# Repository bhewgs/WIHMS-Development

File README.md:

# WIHMS-Development

This repository serves as the open source location for development of the Wearable Integrated Health Monitoring System (WIHMS) garment. This effort was funded by the Vermont Space Grant Consortium under NASA Cooperative Agreement NNX15AP86H. Sensors currently incorporated in the garment are linked below:  
Gravity 3 Lead Heart Rate Monitor: https://amzn.to/2YntU75  
MAXIM30102 Particle Sensor: https://amzn.to/2Srb2R8  
Vishay Thermistor: https://bit.ly/3b1BSWt  
SSD1306 128x32 OLED Display: https://amzn.to/35nHatQ  
DS3231 Real Time Clock: https://amzn.to/3d59WSF  
Moisture Sensor Custom Board: https://github.com/bhewgs/WIHMS-Development/tree/master/MoistureSensor  
Data Consolidation Board Design Files: https://github.com/bhewgs/WIHMS-Development/tree/master/Version%202%20SOIC8%20TCA9517  

Blake Hewgill, MS Student
Jeff Frolik, EBE Department Chair
Ryan McGinnis, Faculty Advisor
M-Sense Research Group: https://www.uvm.edu/~rsmcginn/  
Sensor Networks and Wireless Laboratory   
Direct correspondence to Blake Hewgill: bhewgill94@gmail.com

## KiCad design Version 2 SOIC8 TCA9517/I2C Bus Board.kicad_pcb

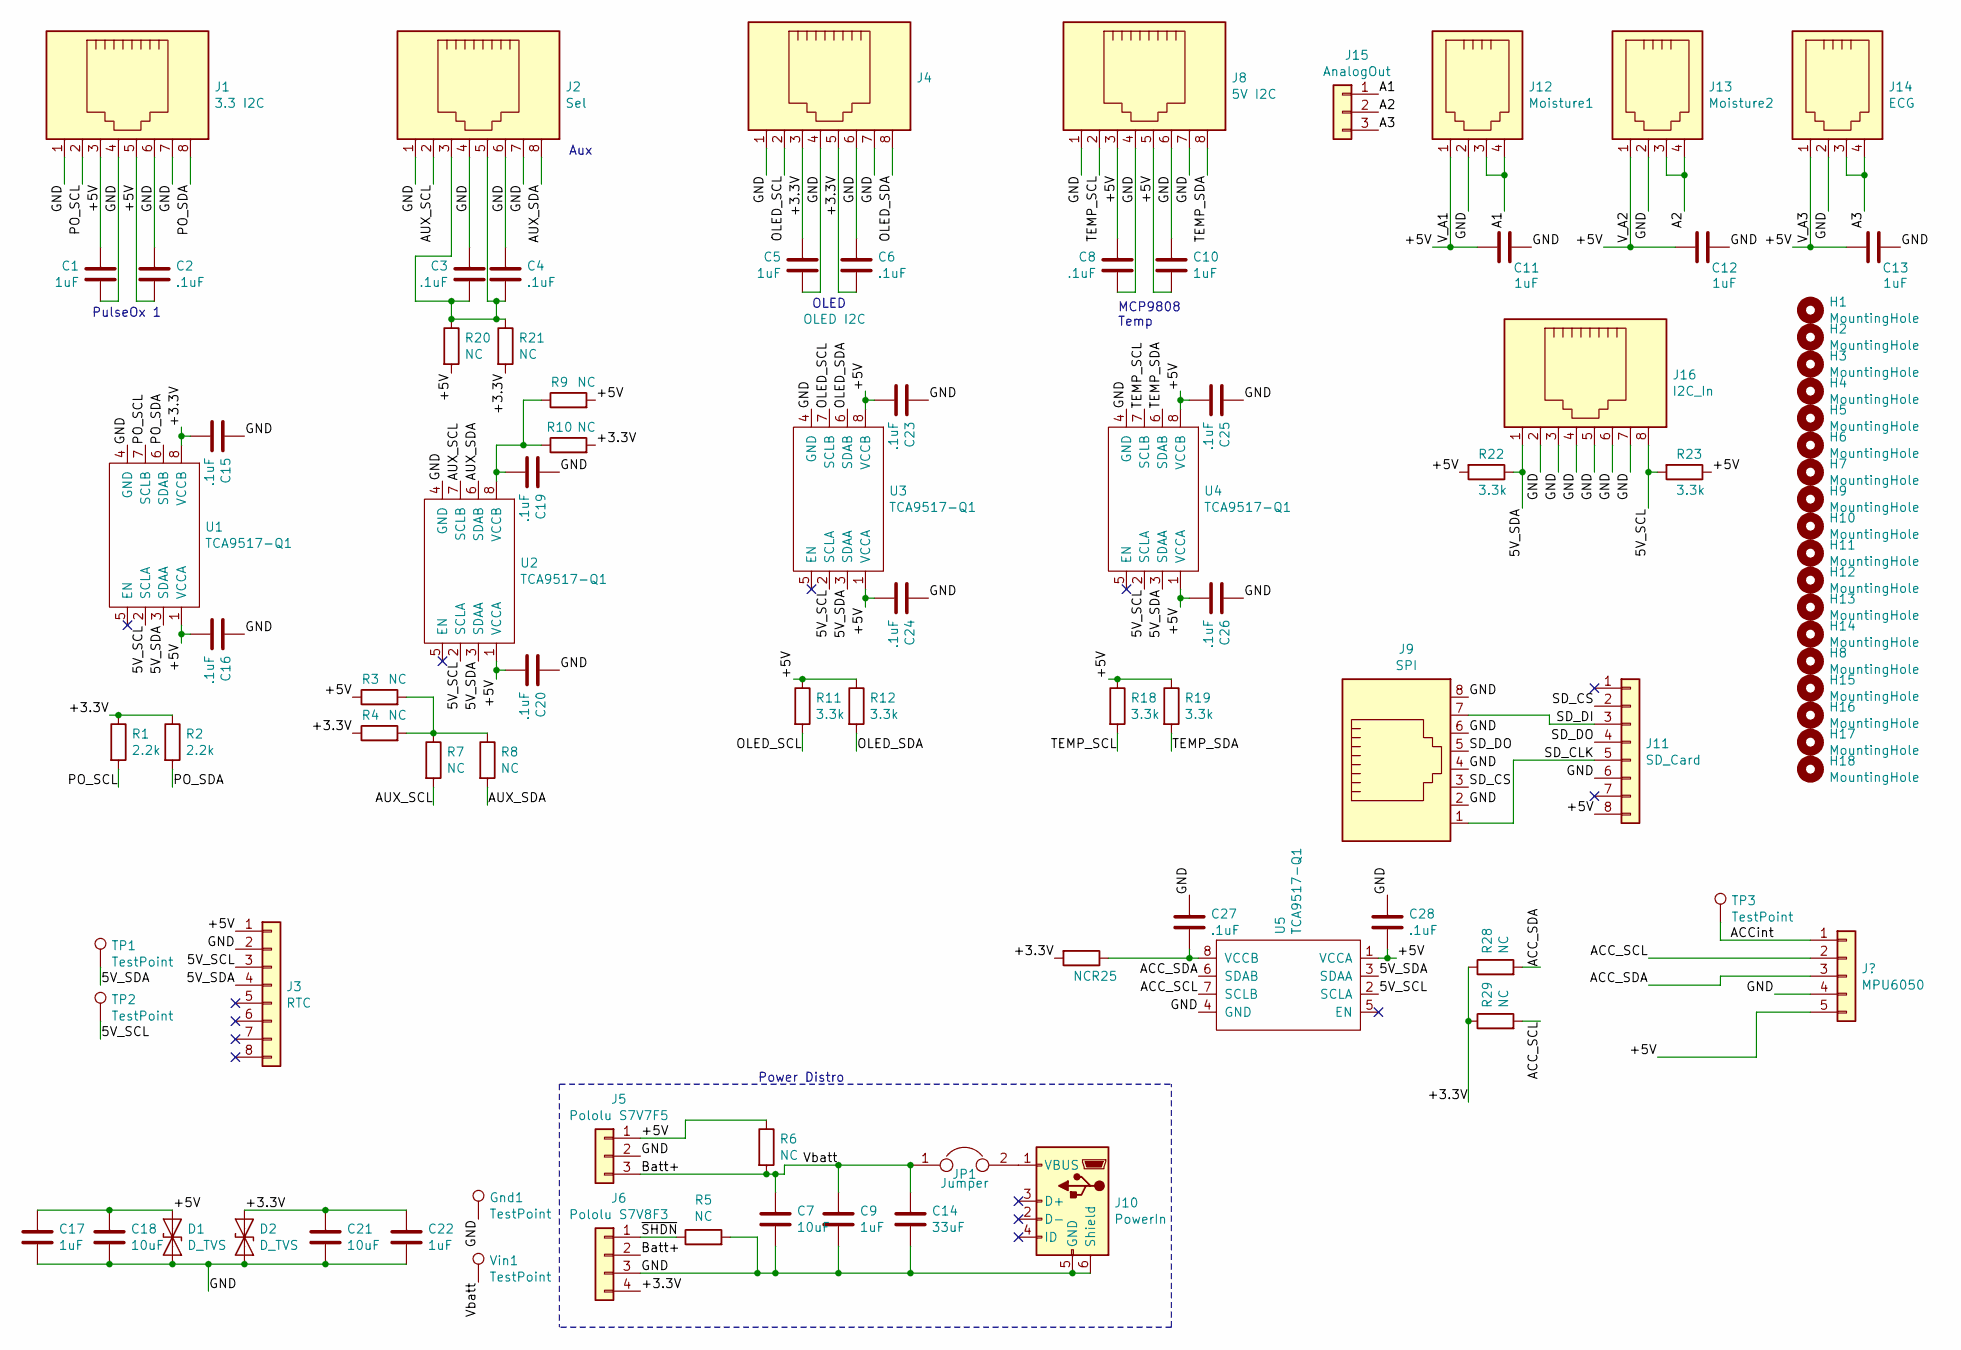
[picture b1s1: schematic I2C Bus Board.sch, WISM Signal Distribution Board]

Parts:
C1, C5, C9, C10, C11, C12, C13, C17, C22: 1uF; C_0603_1608Metric_Pad1.05x0.95mm_HandSolder
C2, C3, C4, C6, C8, C15, C16, C19, C20, C23, C24, C25, C26, C27, C28: .1uF; C_0603_1608Metric_Pad1.05x0.95mm_HandSolder
C7, C18, C21: 10uF; C_0603_1608Metric_Pad1.05x0.95mm_HandSolder
C14: 33uF; C_0805_2012Metric_Pad1.15x1.40mm_HandSolder
D1, D2: D_TVS; D_1206_3216Metric_Pad1.42x1.75mm_HandSolder
Gnd1: TestPoint; TestPoint_Loop_D1.80mm_Drill1.0mm_Beaded
H1, H2, H3, H4, H5, H6, H7, H8, H9, H10, H11, H12, H13, H14, H15, H16, H17, H18: MountingHole; MountingHole_2.2mm_M2
J1: 3.3 I2C; RJ45_Amphenol_54602-x08_Horizontal
J2: Sel; RJ45_Amphenol_54602-x08_Horizontal
J3: RTC; PinHeader_1x08_P2.54mm_Vertical
J4: OLED I2C; RJ45_Amphenol_54602-x08_Horizontal
J5: Pololu S7V7F5; PinHeader_1x03_P2.54mm_Vertical
J6: Pololu S7V8F3; PinHeader_1x04_P2.54mm_Vertical
J8: 5V I2C; RJ45_Amphenol_54602-x08_Horizontal
J9: SPI; RJ45_Amphenol_54602-x08_Horizontal
J10: PowerIn; USB_Micro-B_Wuerth_629105150521_CircularHoles
J11: SD_Card; PinHeader_1x08_P2.54mm_Vertical
J12: Moisture1; 4p4c
J13: Moisture2; 4p4c
J14: ECG; 4p4c
J15: AnalogOut; PinHeader_1x03_P2.54mm_Vertical
J16: I2C_In; RJ45_Amphenol_54602-x08_Horizontal
JP1: Jumper; PinHeader_1x02_P2.54mm_Vertical
R1, R2: 2.2k; R_0603_1608Metric_Pad1.05x0.95mm_HandSolder
R3, R4, R5, R7, R8, R9, R10, R20, R21, R25, R28, R29: NC; R_0603_1608Metric_Pad1.05x0.95mm_HandSolder
R6: NC; SolderJumper-2_P1.3mm_Open_RoundedPad1.0x1.5mm
R11, R12, R18, R19, R22, R23: 3.3k; R_0603_1608Metric_Pad1.05x0.95mm_HandSolder
TP1, TP2, TP3: TestPoint; TestPoint_Loop_D1.80mm_Drill1.0mm_Beaded
U1, U2, U3, U4, U5: TCA9517-Q1; SOIC-8_3.9x4.9mm_P1.27mm
Vin1: TestPoint; TestPoint_Loop_D1.80mm_Drill1.0mm_Beaded

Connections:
/5V_SCL: J3.3, J16.8, R23.2, TP2.1, U1.2 (SCLA), U2.2 (SCLA), U3.2 (SCLA), U4.2 (SCLA), U5.2 (SCLA)
/5V_SDA: J3.4, J16.1, R22.1, TP1.1, U1.3 (SDAA), U2.3 (SDAA), U3.3 (SDAA), U4.3 (SDAA), U5.3 (SDAA)
/A1: J12.3, J12.4, J15.1
/A2: J13.3, J13.4, J15.2
/A3: J14.3, J14.4, J15.3
/ACC_SCL: R29.2, U5.7 (SCLB); also elsewhere on the board
/ACC_SDA: R28.2, U5.6 (SDAB); also elsewhere on the board
/ACCint: TP3.1; also elsewhere on the board
/AUX_SCL: J2.2, R7.2, U2.7 (SCLB)
/AUX_SDA: J2.8, R8.2, U2.6 (SDAB)
/Batt+: C7.1, C9.1, C14.1, J5.3, J6.2, JP1.1, R6.2, Vin1.1
/GND: C1.1, C2.1, C3.2, C4.1, C5.1, C6.1, C7.2, C8.1, C9.2, C10.1, C11.1, C12.1, C13.1, C14.2, C15.1, C16.1, C17.2, C18.2, C19.1, C20.1, C21.2, C22.2, C23.1, C24.1, C25.1, C26.1, C27.1, C28.1, D1.2 (A2), D2.2 (A2), Gnd1.1, J1.1, J1.4, J1.6, J1.7, J2.1, J2.4, J2.6, J2.7, J3.2, J4.1, J4.4, J4.6, J4.7, J5.2, J6.3, J8.1, J8.4, J8.6, J8.7, J9.2, J9.4, J9.6, J9.8, J10.5 (GND), J10.6 (Shield), J11.6, J12.2, J13.2, J14.2, J16.2, J16.3, J16.4, J16.5, J16.6, J16.7, R5.2, U1.4 (GND), U2.4 (GND), U3.4 (GND), U4.4 (GND), U5.4 (GND); also elsewhere on the board
/OLED_SCL: J4.2, R11.2, U3.7 (SCLB)
/OLED_SDA: J4.8, R12.2, U3.6 (SDAB)
/PO_SCL: J1.2, R1.2, U1.7 (SCLB)
/PO_SDA: J1.8, R2.2, U1.6 (SDAB)
/SD_CLK: J9.1, J11.5
/SD_CS: J9.3, J11.2
/SD_DI: J9.7, J11.3
/SD_DO: J9.5, J11.4
/TEMP_SCL: J8.2, R18.2, U4.7 (SCLB)
/TEMP_SDA: J8.8, R19.2, U4.6 (SDAB)
/~SHDN: J6.1, R5.1
unnamed: C3.1, C4.2, J2.3, J2.5, R20.1, R21.1
unnamed: C19.2, R9.1, R10.1, U2.8 (VCCB)
unnamed 25: C27.2, R25.1, U5.8 (VCCB); also elsewhere on the board
unnamed: J10.1 (VBUS), JP1.2
unnamed: R3.2, R4.2, R7.1, R8.1

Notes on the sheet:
MCP9808 Temp
PulseOx 1
Aux
Power Distro
OLED

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
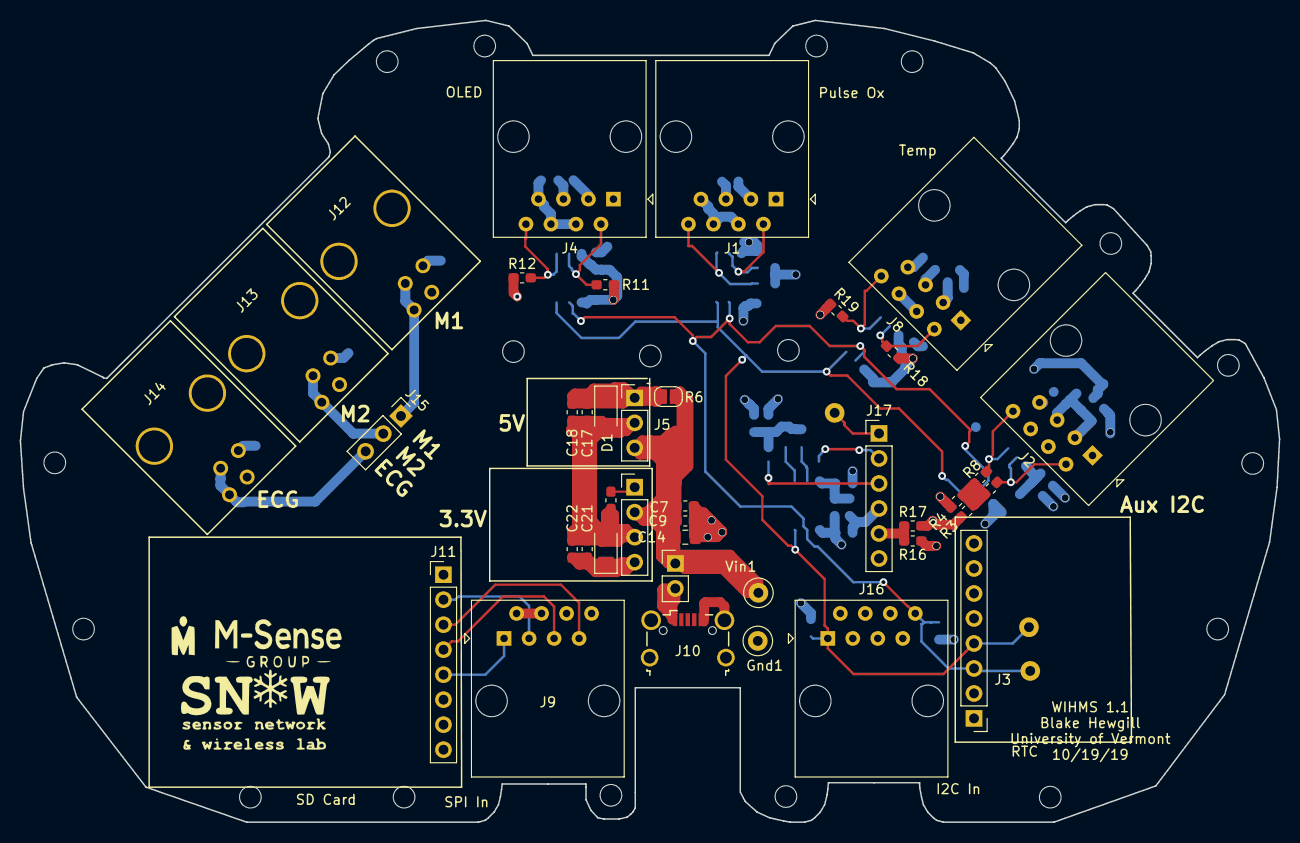
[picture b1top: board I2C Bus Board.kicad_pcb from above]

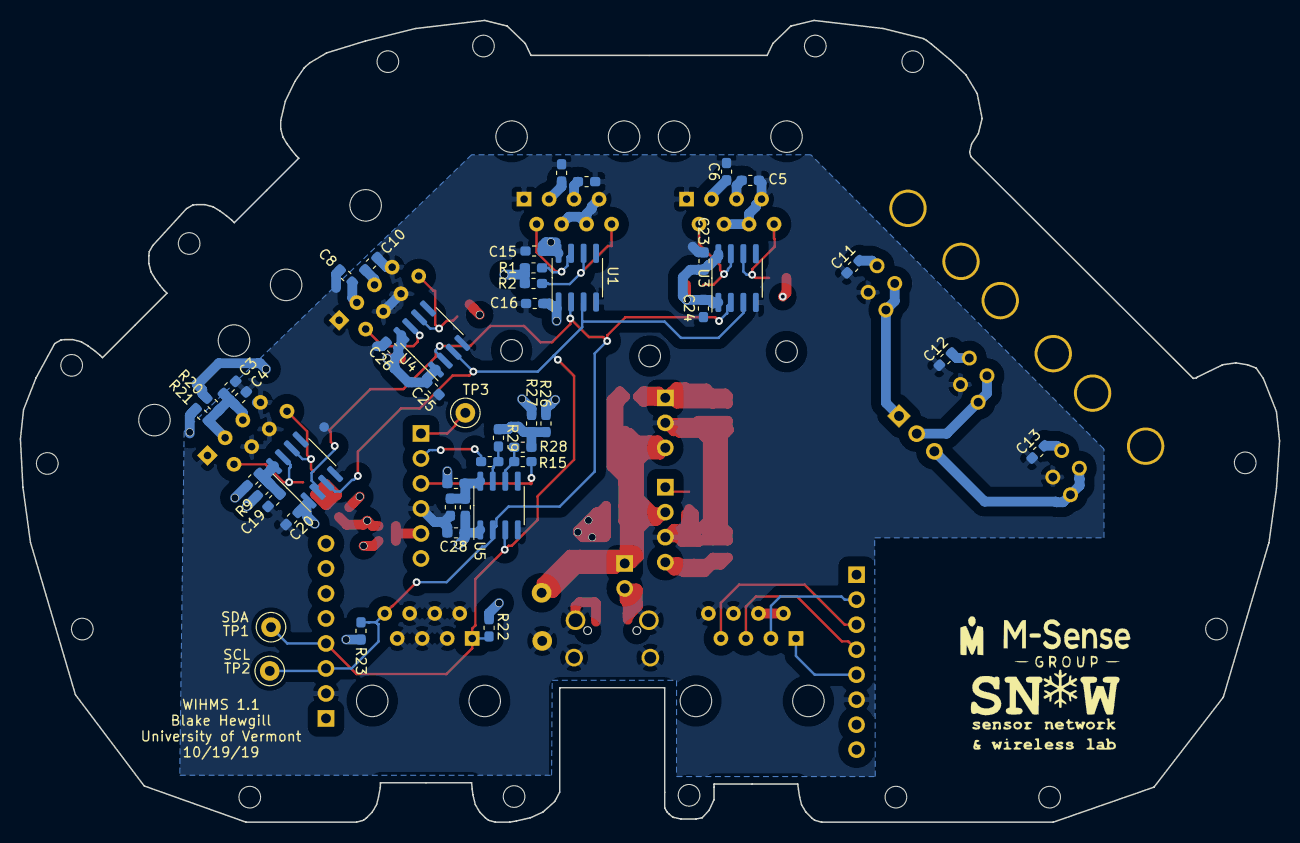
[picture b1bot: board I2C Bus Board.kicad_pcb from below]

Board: 4 copper layers, 128.0 x 81.5 mm, 103 parts (45 on the bottom side), 34 nets.

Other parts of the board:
J17: MPU6050; PinHeader_1x06_P2.54mm_Vertical
R14, R15, R16, R17, R24: 0; R_0603_1608Metric_Pad1.05x0.95mm_HandSolder
R26, R27: NC; R_0603_1608Metric_Pad1.05x0.95mm_HandSolder

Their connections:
/ACC_SCL: R14.2; also elsewhere on the board
/ACC_SDA: R15.2; also elsewhere on the board
/ACCint: J17.1; also elsewhere on the board
/GND: J17.4; also elsewhere on the board
unnamed 25: R24.1; also elsewhere on the board
unnamed: J17.2, R14.1
unnamed: J17.3, R15.1
unnamed: J17.5, R16.1, R17.1

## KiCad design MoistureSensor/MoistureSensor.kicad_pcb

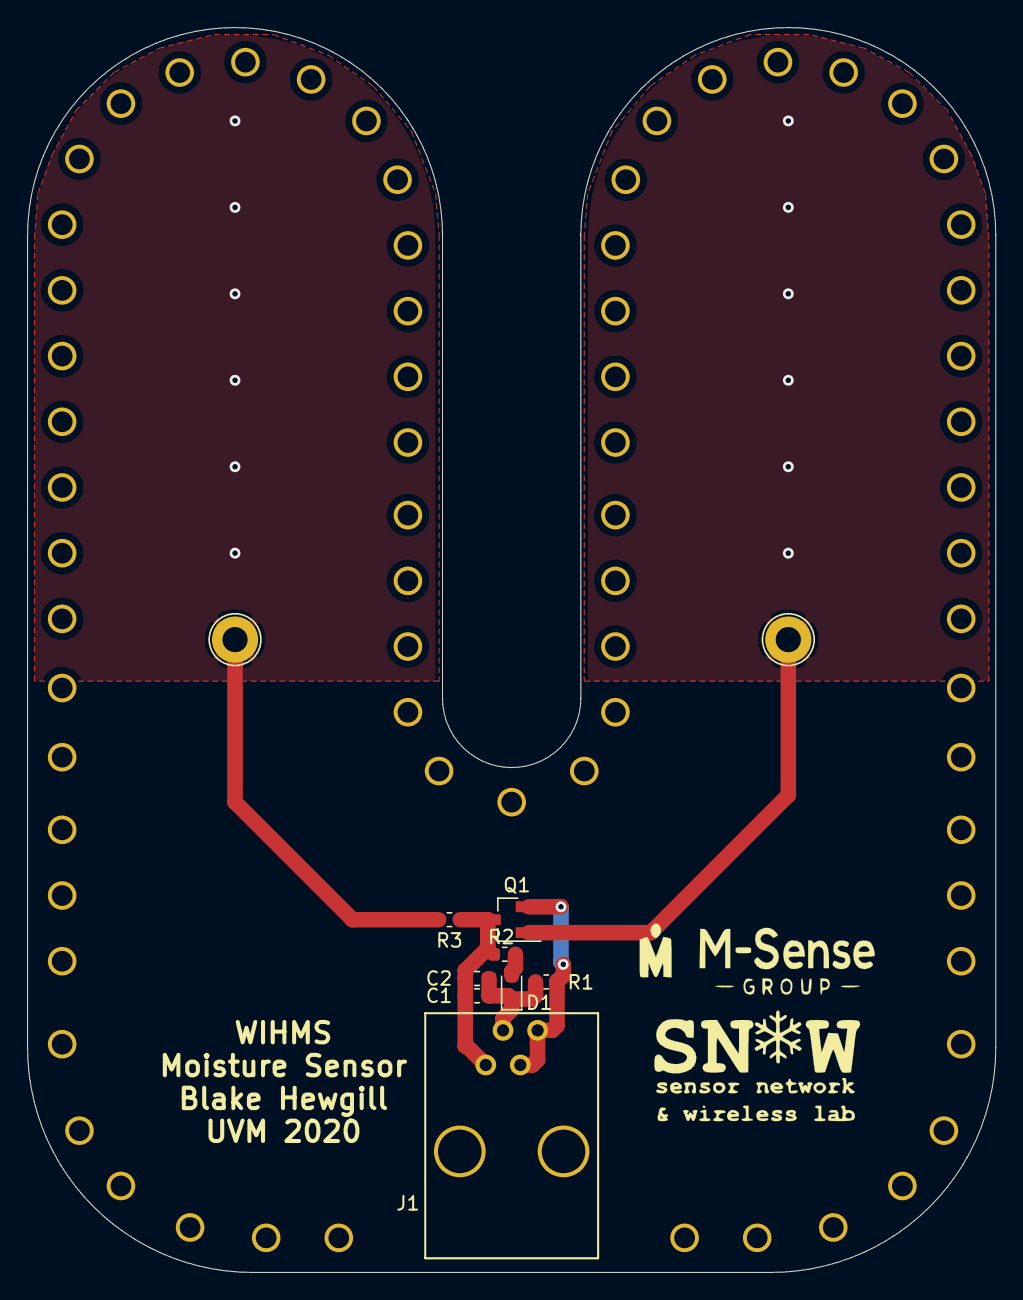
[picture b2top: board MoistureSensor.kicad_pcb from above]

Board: 2 copper layers, 71.1 x 91.4 mm, 10 parts (0 on the bottom side), 6 nets.

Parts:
C1, C2: C; C_0603_1608Metric_Pad1.05x0.95mm_HandSolder
D1: LED; LED_0603_1608Metric_Pad1.05x0.95mm_HandSolder
J1: 4P4C; 4p4c
LEAD1: Lead2; TestPoint_Loop_D2.50mm_Drill1.85mm
LEAD2: Lead1; TestPoint_Loop_D2.50mm_Drill1.85mm
Q1: S8050; SOT-23_Handsoldering
R1, R3: R; R_0603_1608Metric
R2: NC; R_0603_1608Metric

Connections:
/V+: C1.1, C2.1, J1.1, Q1.3, R2.2, R3.2
/Vsense: J1.3, J1.4, Q1.2, R1.2
GND: C1.2, C2.2, D1.1, J1.2, R1.1
unnamed: D1.2, R2.1
unnamed: LEAD1.1, Q1.1
unnamed: LEAD2.1, R3.1

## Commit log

2020-05-01 Add files via upload
    Moisture sensor design files added to the repo
2020-05-01 Add files via upload
    This is current code running the WIHMS system
2020-05-01 Data consolidation PCB files
2020-05-01 README file
2020-05-16 MAX30102 Breakout to CAT6e
2020-07-10 Embedded code initial commit
2020-07-13 Matlab functions and scripts for data analysis
2020-07-13 Raw binary files created by the WIHMS garment.
2020-08-13 MATLAB models for stress prediction
